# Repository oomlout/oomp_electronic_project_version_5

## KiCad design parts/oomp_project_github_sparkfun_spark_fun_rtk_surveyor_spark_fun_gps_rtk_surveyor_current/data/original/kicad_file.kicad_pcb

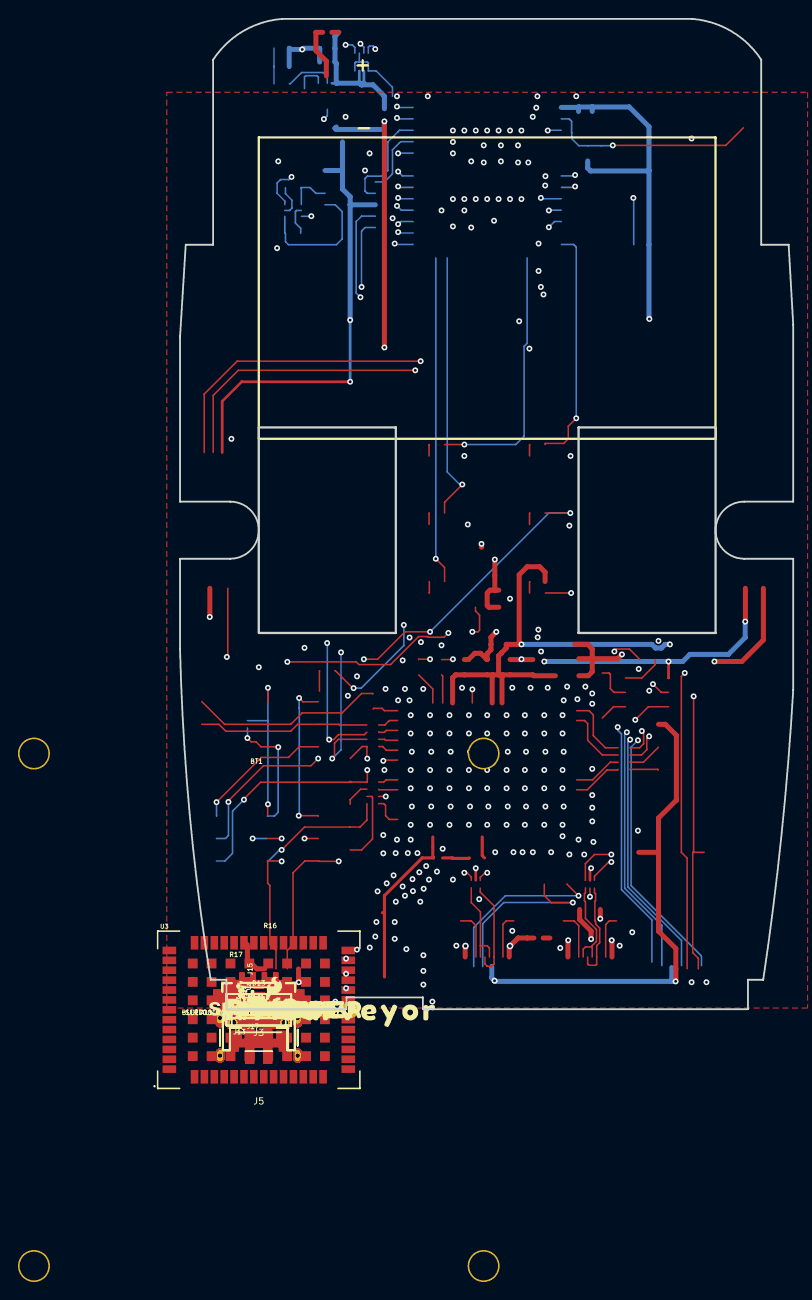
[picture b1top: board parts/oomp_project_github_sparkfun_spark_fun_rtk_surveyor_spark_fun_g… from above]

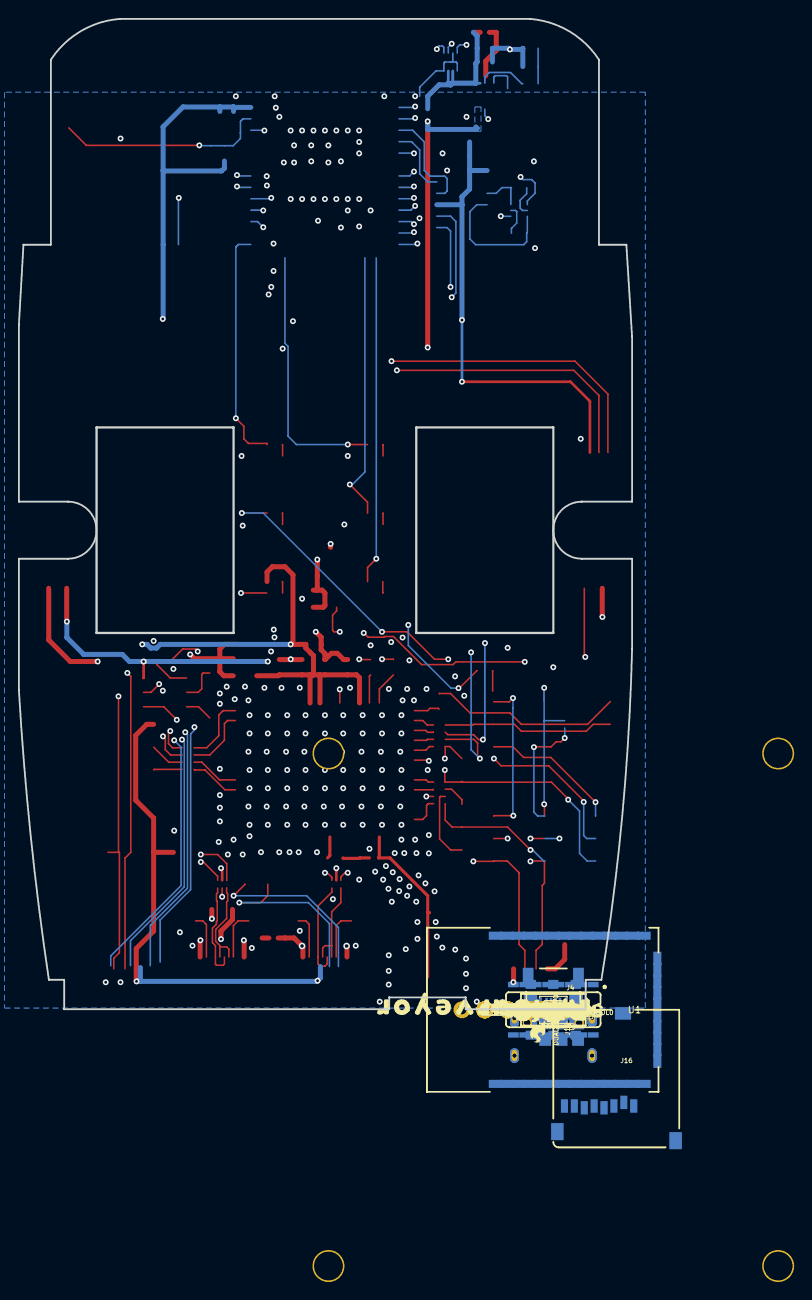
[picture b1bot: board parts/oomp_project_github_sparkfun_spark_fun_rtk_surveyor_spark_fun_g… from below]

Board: 4 copper layers, 68.2 x 110.1 mm, 199 parts (55 on the bottom side), 95 nets.

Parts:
BLUETOOTH_BROADCAST0: SWITCH_DPDT_SMD_AYZ0202
BT1: LIPO-OUTLINE1000; LIPO-1000
C1: 47pF; 0402
C2, C4, C6, C17, C18: 1.0uF; 0603
C5, C7, C11, C12, C13, C15, C16: 0.1uF; 0603
C8, C9: 4.7uF; 0603
C10, C14: 10uF; 0603
D1: Yellow; LED-0603
D2, D6: PRTR5V0U2F; SOT886
D3: WHITE; LED-0603
D4: BLUE; LED-0603
D7, D9: 3A/10V/280mV; SOD-323
D8, D10, D11: GREEN; LED-0603
D12: RED; LED-0603
D13: LED-TRICOLOR-5050
D14: PESD0402; 0402
DUAL_OUTPUT0: SMT-JUMPER_2_NO_SILK
E1: SMA; SMA-EDGE
FB1: 2.66Ω; 0402-TIGHT
FRAME1: FRAME-LETTERNO_PACKAGE; DUMMY
FRAME2: FRAME-LEDGER; CREATIVE_COMMONS
J1, J11, J12: 1X04_NO_SILK
J2, J9: JST-4-SMD-1.25MM-LOCKING
J3, J5: USB Female Type C Connector; USB-C-16P_4LAYER-PADS
J4: Qwiic Right Angle; JST04_1MM_RA
J6: Start Base; JST-2-SMD
J7: Power Switch; JST-2-SMD
J8: JST-2-SMD
J10, J14, J15: 1X02_NO_SILK
J13: Internal; JST04_1MM_RA
J16: microSD; MICRO-SD-SOCKET
J17: Qwiic Right Angle; 1X04_NO_SILK
J18: 1X05_NO_SILK
JP21, JP61, JP71, JP81: FIDUCIALUFIDUCIAL; FIDUCIAL-MICRO
LOGO1: OSHW-LOGOMINI; OSHW-LOGO-MINI
LOGO2, LOGO3: SFE_LOGO_NAME_FLAME.1_INCH; SFE_LOGO_NAME_FLAME_.1
MEAS0, MEAS1: COMBO-JUMPER_2_NC_TRACE
Q2: MBT3904DW1T1; SC70-6
R1: 4.7k; 0603
R2, R4, R9: 33; 1206_RA
R3: 33; 0603
R5: 0; 0603
R6, R7, R8: 1k; 0603
R10, R12, R34: 330; 0603
R11, R24, R25, R26: 20; 0603
R13, R15: 100k; 0603
R14: 10; 0603
R16, R17, R37, R38: 5.1k; 0603
R18, R20, R23, R29: 10k; 0603
R27, R28: 27; 0603
R30: 150k; 0603
SERIAL1_CONNECTION0: SWITCH_DPDT_SMD_AYZ0202
U1: ESP-WROOM-3232D-NARROW; ESP-WROOM-32D-NARROW
U2, U4: 3.3V; SOT23-5
U3: U-BLOX_ZED-F9P; ZED-F9P
U6: CH340C; SO016
U7: MAX17048; DFN-8
U10: MCP73833; DFN-10
U$1, U$38, U$48, U$82: #GND#0
U$2: SPECIAL_INSTRUCTIONS-ORDERING; ORDERING_INSTRUCTIONS
U$3, U$34: ROCKER_SWITCH
U$4: #BASE#0
U$5, U$37, U$47: #3V3#0
U$6: ANTENNA0
U$7, U$74: RTK0
U$8: #CHG#0
U$9, U$71: _SURVEYOR3
U$10: #RTK#1
U$11: #PPS#0
U$12: #RTK#0
U$13, U$15, U$21, U$69, U$75, U$76, U$77, U$78: LIGHT_PIPE_3MM
U$14: #RX#2
U$16: ZED0
U$17: ##SAFE##5
U$18: ACTIVE0
U$19: L1#L21
U$20: #PAIR#0
U$22: BASE2
U$23: #3#5#5V#0
U$24: #PPS#1
U$25: #PWR#2
U$26: 1553DBK-ENCLOSURE
U$27: LIPO0
U$28: ##RST##4
U$29, U$63: SERIAL10
U$30, U$93: QWIIC_4MM
U$31: OFF1
U$32: #FENCE#3
U$33: #INT#0
U$35: U#BLOX0
U$36, U$66: USB1
U$39: #RX2#2
U$40: #TX2#1
U$41: BLUETOOTH2
U$42: ON0
U$43: SERIAL20
U$44: ROVER3
U$45, U$68: #RX1#2
U$46, U$65: #TX1#1
U$49, U$52: NMEA1
U$50: RADIO0
U$51: BROADCAST3
U$53: RTCM0
U$54: BASE0
U$55, U$57: SWITCH1
U$56: POWER0
U$58: BLUEOOTH3
U$59: CNTR1
U$60: #ESP_RST#0
U$61: EXT0
U$62: NMEA2
U$64: CONNECTION1
U$67: ESP320
U$70: #GND#2
U$72: #TX#1
U$73: #DUAL#0
U$79: #1CM#0
U$80: #10CM#1
U$81: #100CM#2
U$83: MICROSD0
U$84: #GND#1
U$85: #3V3#2
U$86: #SCL#1
U$87: #SDA#0
U$88: #D_SEL#0
U$89: DATA2
U$90: PORT3
U$91: PPS#RESET0
U$92: NMEA#SERIAL1
U$94, U$95: V170
ZED_CONTROL0: SWITCH_DPDT_SMD_AYZ0202

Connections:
3.3V: C2.1, C4.1, C5.2, C7.2, C10.1, C11.1, C13.1, C14.1, C16.1, J1.4, J2.1, J4.2, J12.4, J13.2, J16.VCC, J17.2, R12.2, R13.2, R15.2, R20.2, U1.2, U2.5, U3.33, U3.34, U3.38, U6.4, U6.16
5V: C6.1, J7.1, J9.1, J11.4, U2.1, U2.3
ANT_VCC: C1.1, FB1.2, R14.1
BACKUP: C18.1, U3.36, U4.5
CC1: J5.A5, R17.2
CC2: J5.B5, R16.2
CC3: J3.B5, R37.2
CC4: J3.A5, R38.2
CHG_LED: R1.2, U10.3
CHG_THERM1: R5.2, R18.2, R30.2
D+: D6.4, R27.1
D+1: D2.4, U6.5
D-: D6.6, R28.1
D-1: D2.6, U6.6
ESP32_EN: C12.1, J14.1, Q2.3, R20.1, U1.3
ESP32_RXI: U1.34, U6.2
ESP32_TXO: U1.35, U6.3
ESP32_~DTR: Q2.1, R23.1, U6.13
ESP32_~RTS: Q2.4, R29.1, U6.14
ESP_0/BOOT: Q2.6, U1.25
ESP_2/LED_1CM: R26.1, U1.24
ESP_4/LED_BASE_STAT: R34.1, U1.26
ESP_5/SWITCH_BASE_SELECT: J6.1, U1.29
ESP_12/LED_BLUETOOTH: R10.1, U1.14
ESP_13/LED_100CM: R24.1, U1.16
ESP_15/LED_10CM: R25.1, U1.23
ESP_16/BT_RXI: BLUETOOTH_BROADCAST0.2, U1.27
ESP_17/BT_TXO: BLUETOOTH_BROADCAST0.5, U1.28
ESP_18/SD_SCK: J16.SCLK, U1.30
ESP_19/SD_CIPO: J16.DO/DAT0, U1.31
ESP_21/SDA: J4.3, J13.3, J17.3, R9.P6, U1.33, U7.8
ESP_22/SCL: J4.4, J13.4, J17.4, R9.P7, U1.36, U7.7
ESP_23/SD_COPI: J16.DI/CMD, U1.37
ESP_25/SD_~CS: J16.CS/DAT3, R13.1, U1.10
ESP_26/ZED_TX_READY: J18.1, R9.P8, U1.11
ESP_26/ZED_TX_READY_LV: R9.P1, U3.46
ESP_27/ZED_~RESET: J18.2, R2.P5, U1.12, ZED_CONTROL0.4
ESP_27/ZED_~RESET_LV: R2.P4, U3.49
ESP_32/PWR_LVL_RED: D13.5, U1.8
ESP_33/PWR_LVL_GRN: D13.4, U1.9
ESP_36/BATT_ALRT: U1.4, U7.5
ESP_D1+: D2.3, J3.A6, J3.B6
ESP_D1-: D2.1, J3.A7, J3.B7
EXTERNAL_SERIAL1_RXI: SERIAL1_CONNECTION0.4, ZED_CONTROL0.6
EXTERNAL_SERIAL1_RXI/ZED_~RESET: J2.3, J12.2, ZED_CONTROL0.5
EXTERNAL_SERIAL1_TXO: DUAL_OUTPUT0.2, SERIAL1_CONNECTION0.1, ZED_CONTROL0.3
EXTERNAL_SERIAL1_TXO/PPS: J2.2, J12.3, ZED_CONTROL0.2
FENCE_LV: R4.P8, U3.19
GND: C1.2, C2.2, C4.2, C5.1, C6.2, C7.1, C8.2, C9.2, C10.2, C11.2, C12.2, C13.2, C14.2, C15.2, C16.2, C17.2, C18.2, D1.C, D2.2, D4.C, D6.2, D8.C, D10.C, D11.C, D12.C, D14.2, E1.GND@0, E1.GND@1, E1.GND@2, E1.GND@3, J1.1, J2.4, J3.GND, J3.GND2, J3.SHLD1, J3.SHLD2, J3.SHLD3, J3.SHLD4, J4.1, J5.GND, J5.GND2, J5.SHLD1, J5.SHLD2, J5.SHLD3, J5.SHLD4, J6.2, J8.1, J9.4, J10.2, J11.1, J12.1, J13.1, J14.2, J16.CD1, J16.GND, J16.GND1, J16.GND3, J17.1, R6.2, R7.1, R8.2, R15.1, R16.1, R17.1, R18.1, R30.1, R37.1, R38.1, U1.1, U1.15, U1.38, U1.GND1, U1.GNDT1, U1.GNDT2, U1.GNDT3, U1.GNDT4, U1.GNDT5, U1.GNDT6, U1.GNDT7, U1.GNDT8, U2.2, U3.1, U3.3, U3.12, U3.14, U3.32, U3.37, U3.41, U3.48, U3.55, U3.56, U3.57, U3.58, U3.59, U3.60, U3.61, U3.62, U3.63, U3.64, U3.65, U3.66, U3.67, U3.68, U3.69, U3.70, U3.71, U3.72, U3.73, U3.74, U3.75, U3.76, U3.77, U3.78, U3.79, U3.80, U3.81, U3.82, U3.83, U3.84, U3.85, U3.86, U3.87, U3.88, U3.89, U3.90, U3.91, U3.92, U3.93, U3.94, U3.95, U3.96, U3.97, U3.98, U3.99, U3.100, U3.101, U3.102, U4.2, U6.1, U7.1, U7.4, U7.6, U7.9, U10.5, U10.11
GPS_ANT1: D14.1, E1.SIG, FB1.1, U3.2
LIPO_RAW: J8.2, MEAS1.1, MEAS1.3
unnamed: D3.A, R12.1
unnamed: D1.A, R11.1
unnamed: D4.A, R10.2
unnamed: J5.VBUS1, J5.VBUS2, MEAS0.1, MEAS0.3
unnamed: R5.1, U10.8
unnamed: D13.1, R1.1
unnamed: D13.3, R6.1
unnamed: D13.2, R8.1
unnamed: R27.2, U3.40
unnamed: R28.2, U3.39
unnamed: R14.2, U3.7
unnamed: Q2.5, R23.2
unnamed: Q2.2, R29.2
unnamed: D8.A, R24.2
unnamed: D10.A, R25.2
unnamed: D11.A, R26.2
unnamed: D12.A, R34.2
unnamed: D9.A, J3.VBUS1, J3.VBUS2
NMEA-RX: BLUETOOTH_BROADCAST0.6, SERIAL1_CONNECTION0.6
NMEA-TX: BLUETOOTH_BROADCAST0.3, DUAL_OUTPUT0.1, SERIAL1_CONNECTION0.3
PPS: R2.P1, U3.53
PROG1: R7.2, U10.6
RTK_LV: R4.P7, U3.20
RX2_LV: R4.P6, U3.26
RXLV: R9.P4, U3.43
SCL_LV: R9.P2, U3.45
SDA_LV: R9.P3, U3.44
TX2_LV: R4.P5, U3.27
TXLV: R3.1, U3.42
UNP_D+: D6.3, J5.A6, J5.B6
UNP_D-: D6.1, J5.A7, J5.B7
VIN: C9.1, D2.5, D6.5, D7.C, D9.C, D13.6, J7.2, MEAS0.2, MEAS0.4, U10.1, U10.2
V_BATT: C8.1, C15.1, C17.1, D7.A, J10.1, MEAS1.2, MEAS1.4, U4.1, U4.3, U7.2, U7.3, U10.9, U10.10
ZED-RXI1: J15.2, R9.P5, SERIAL1_CONNECTION0.5
ZED-RXI2: BLUETOOTH_BROADCAST0.4, J9.3, J11.2, R4.P3
ZED-TXO1: J15.1, R3.2, SERIAL1_CONNECTION0.2
ZED-TXO2: BLUETOOTH_BROADCAST0.1, J9.2, J11.3, R4.P4
ZED_D_SEL: J18.5, R2.P7
ZED_D_SEL_LV: R2.P2, U3.47
ZED_FENCE_STAT: J1.2, R4.P1
ZED_PPS_STAT: J18.4, R2.P8, R11.2, ZED_CONTROL0.1
ZED_RTK_STAT: D3.C, J1.3, R4.P2
ZED_~SAFE: J18.3, R2.P6
ZED_~SAFE_LV: R2.P3, U3.50

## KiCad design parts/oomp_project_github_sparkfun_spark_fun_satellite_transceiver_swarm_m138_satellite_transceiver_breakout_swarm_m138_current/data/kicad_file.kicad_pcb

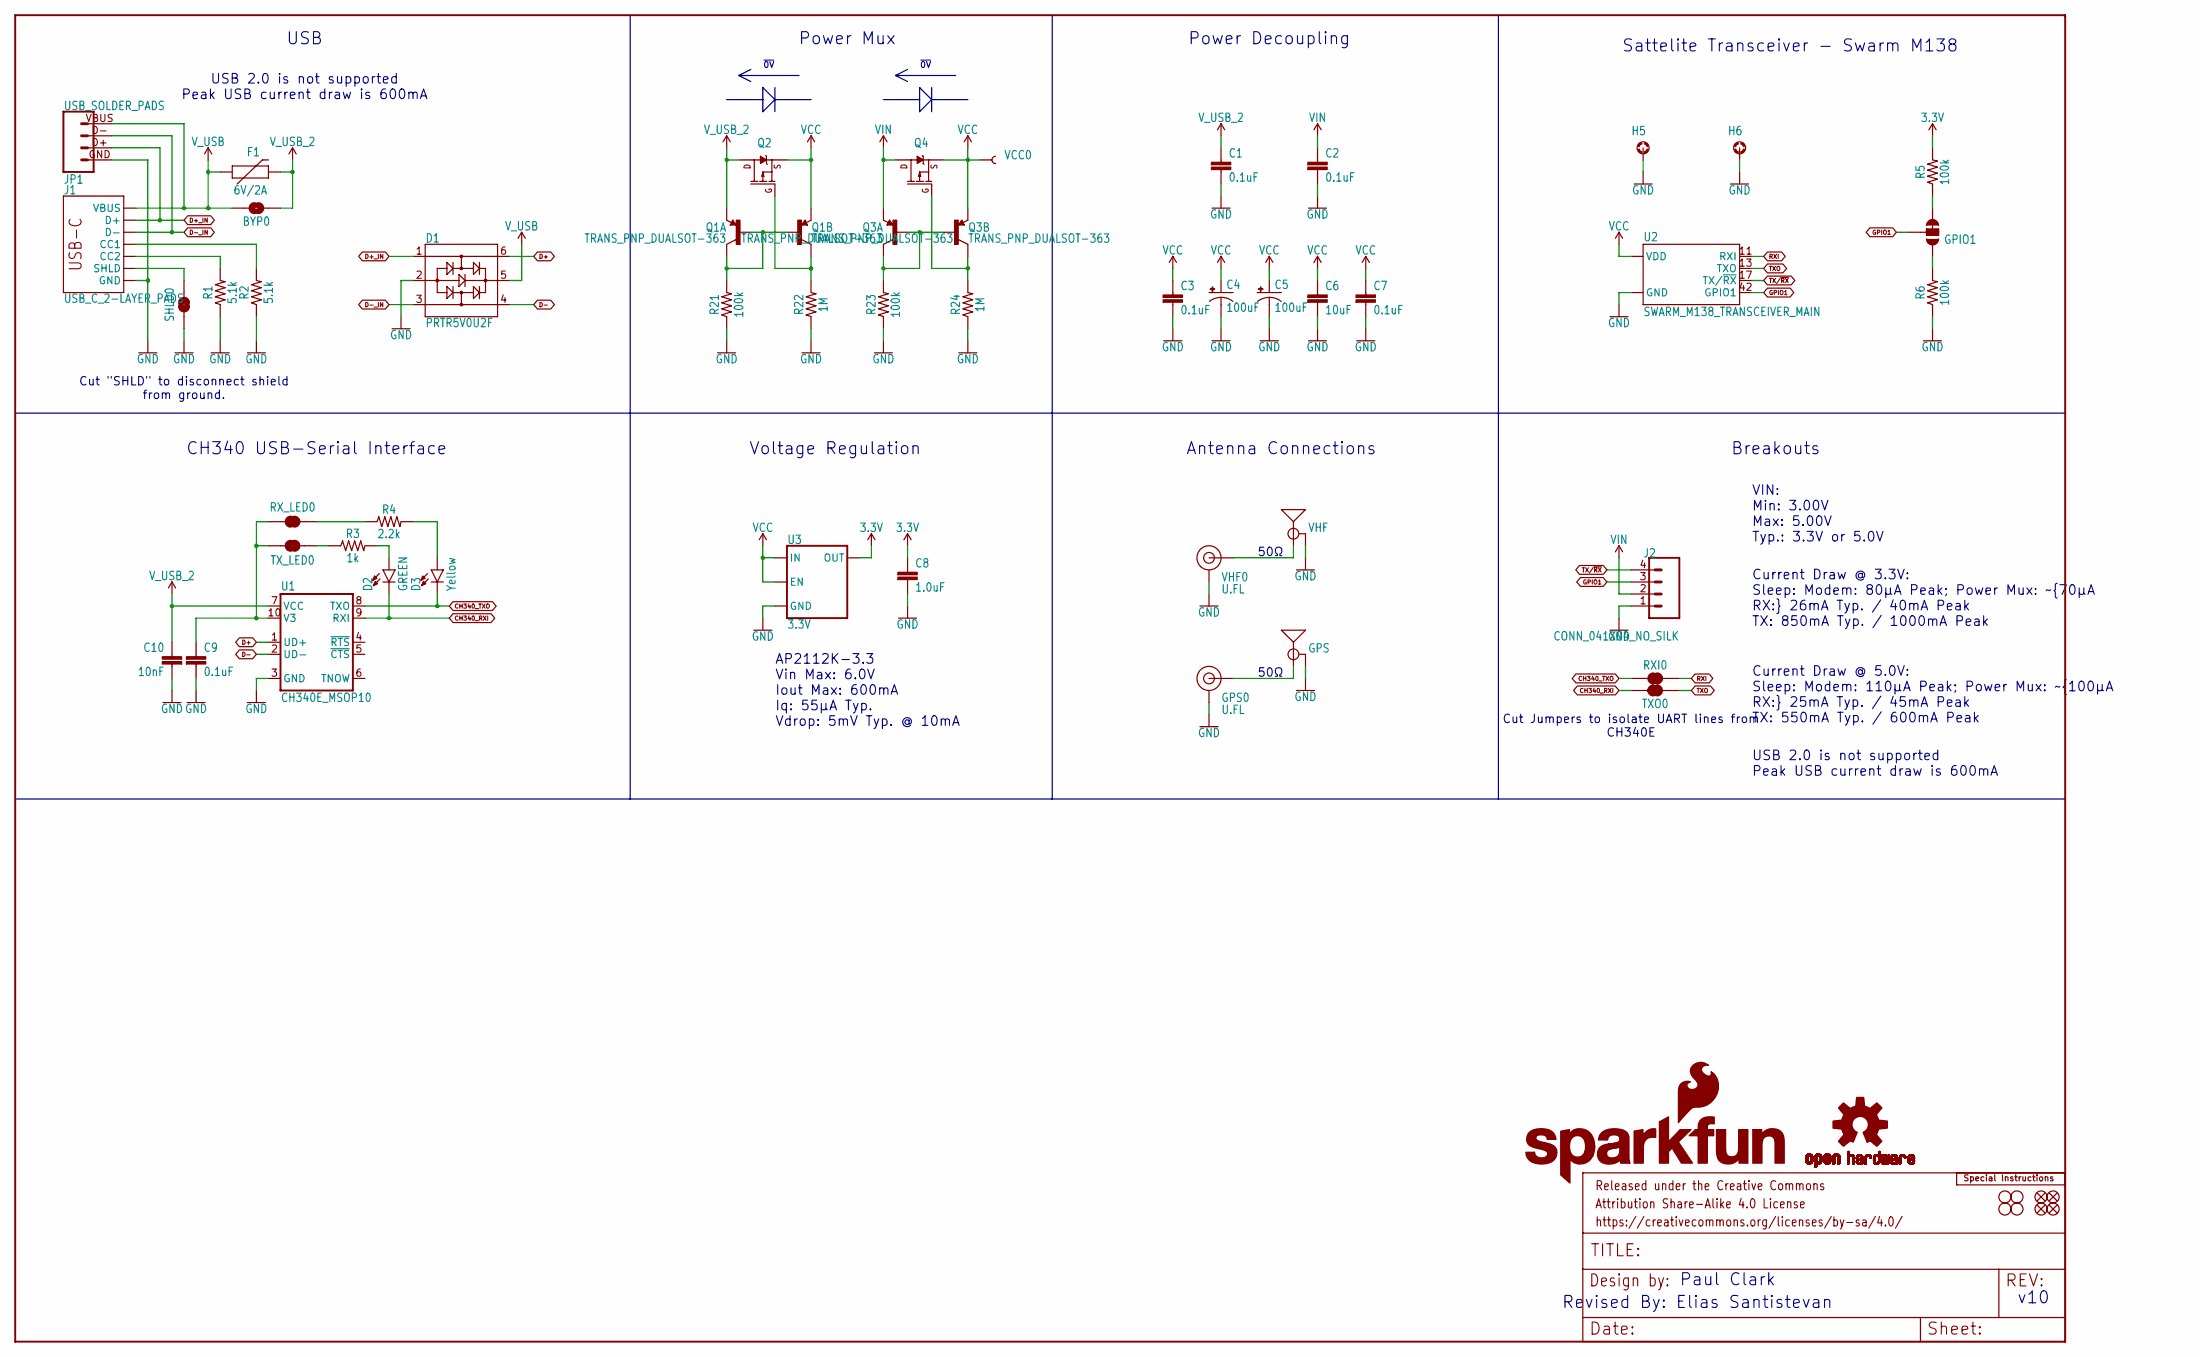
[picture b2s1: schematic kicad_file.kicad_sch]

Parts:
BYP0: JUMPER-SMT_2_NO_SILK; SMT-JUMPER_2_NO_SILK
C1, C2, C3, C7, C9: 0.1uF; 0603
C4, C5: 100uF; PANASONIC_D
C6: 10uF; 0603
C8: 1.0uF; 0603
C10: 10nF; 0603
D1: PRTR5V0U2F; SOT886
D2: GREEN; LED-0603
D3: Yellow; LED-0603
E1: VHF; SMA-EDGE
E2: GPS; SMA-EDGE
F1: 6V/2A; 1210
FD1, FD2, FD3, FD4: FIDUCIAL1X2; FIDUCIAL-1X2
FRAME1: FRAME-LEDGER; CREATIVE_COMMONS
GPIO1: JUMPER-SMT_3_1-NC_TRACE_SILK; SMT-JUMPER_3_1-NC_TRACE_SILK
GPS0: U.FL
H1, H2, H3, H4: STAND-OFF
H5, H6: STAND-OFF-REFLOW-M2.5_1.5MM_TALL; STAND-OFF-REFLOW-M2.5
J1: USB_C_2-LAYER_PADS; USB-C-16P-2LAYER-PADS
J2: CONN_041X04_NO_SILK; 1X04_NO_SILK
JP1: USB_SOLDER_PADS; USB-SOLDER-PADS
LOGO1: SPECIAL_INSTRUCTIONS-ORDERING; ORDERING_INSTRUCTIONS
LOGO2: OSHW-LOGOM; OSHW-LOGO-M
LOGO4: SFE_LOGO_NAME_FLAME.1_INCH; SFE_LOGO_NAME_FLAME_.1
Q1, Q3: TRANS_PNP_DUALSOT-363; SOT363_PHILIPS
Q2, Q4: 20V/4.2A/52mΩ/1.4W; SOT23-3
R1, R2: 5.1k; 0603
R3: 1k; 0603
R4: 2.2k; 0603
R5, R6, R21, R23: 100k; 0603
R22, R24: 1M; 0603
RXI0: JUMPER-COMBO_2_NC_TRACE; COMBO-JUMPER_2_NC_TRACE
RX_LED0: JUMPER-SMT_2_NC_TRACE_SILK; SMT-JUMPER_2_NC_TRACE_SILK
SHLD0: JUMPER-SMT_2_NC_TRACE_SILK; SMT-JUMPER_2_NC_TRACE_SILK
TXO0: JUMPER-COMBO_2_NC_TRACE; COMBO-JUMPER_2_NC_TRACE
TX_LED0: JUMPER-SMT_2_NC_TRACE_SILK; SMT-JUMPER_2_NC_TRACE_SILK
U1: CH340E_MSOP10; MSOP10
U2: SWARM_M138_TRANSCEIVER_MAIN; M.2-SWARM-M138-A
U3: 3.3V; SOT23-5
VCC0: TEST-POINT3X5; PAD.03X.05
VHF0: U.FL

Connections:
3.3V: C8.1, R5.2, U3.5 (OUT)
CH340_RXI: D2.C, TXO0.2, TXO0.4 (2), U1.9 (RXI)
CH340_TXO: D3.C, RXI0.1, RXI0.3 (1), U1.8 (TXO)
D+: D1.6, U1.1 (UD+)
D+_IN: D1.1, J1.A6 (D+), J1.B6 (D+), JP1.D+ (3)
D-: D1.4, U1.2 (UD-)
D-_IN: D1.3, J1.A7 (D-), J1.B7 (D-), JP1.D- (2)
GND: C1.2, C2.2, C3.2, C4.-, C5.-, C6.2, C7.2, C8.2, C9.2, C10.2, D1.2, E1.GND@0 (GND), E1.GND@1 (GND), E1.GND@2 (GND), E1.GND@3 (GND), E2.GND@0 (GND), E2.GND@1 (GND), E2.GND@2 (GND), E2.GND@3 (GND), GPS0.1 (GND), GPS0.2 (GND), H5.1, H6.1, J1.GND, J1.GND2 (GND), J2.1, JP1.GND (4), R1.1, R2.1, R6.1, R21.1, R22.1, R23.1, R24.1, SHLD0.1, U1.3 (GND), U2.4 (GND), U2.9 (GND), U2.15 (GND), U2.18 (GND), U2.21 (GND), U2.26 (GND), U2.27 (GND), U2.29 (GND), U2.34 (GND), U2.35 (GND), U2.37 (GND), U2.40 (GND), U2.43 (GND), U2.50 (GND), U2.A1 (GND), U2.A2 (GND), U3.2 (GND), VHF0.1 (GND), VHF0.2 (GND)
GPIO1: GPIO1.2, J2.3, U2.42 (GPIO1)
GPS: E2.SIG (SIGNAL), GPS0.FEED (SIGNAL)
unnamed: J1.B5 (CC2), R1.2
unnamed: J1.A5 (CC1), R2.2
unnamed: Q1.2 (B), Q1.5 (B), Q1.6 (C), R21.2
unnamed: C9.1, RX_LED0.1, TX_LED0.2, U1.10 (V3)
unnamed: R4.1, RX_LED0.2
unnamed: D2.A, R3.2
unnamed: D3.A, R4.2
unnamed: R3.1, TX_LED0.1
unnamed: Q1.3 (C), Q2.1 (G), R22.2
unnamed: GPIO1.3, R5.1
unnamed: Q3.2 (B), Q3.5 (B), Q3.6 (C), R23.2
unnamed: GPIO1.1, R6.2
unnamed: Q3.3 (C), Q4.1 (G), R24.2
RXI: RXI0.2, RXI0.4 (2), U2.11 (RXI)
SHLD: J1.SHLD1 (SHLD), J1.SHLD2 (SHLD), J1.SHLD3 (SHLD), J1.SHLD4 (SHLD), SHLD0.2
TX/~RX: J2.4, U2.17 (TX/~RX)
TXO: TXO0.1, TXO0.3 (1), U2.13 (TXO)
VCC: C3.1, C4.+, C5.+, C6.1, C7.1, Q1.4 (E), Q2.2 (S), Q3.4 (E), Q4.2 (S), U2.2 (VDD), U2.39 (VDD), U2.41 (VDD), U2.52 (VDD), U3.1 (IN), U3.3 (EN), VCC0.1
VHF: E1.SIG (SIGNAL), VHF0.FEED (SIGNAL)
VIN: C2.1, J2.2, Q3.1 (E), Q4.3 (D)
V_USB: BYP0.2, D1.5, F1.1, J1.VBUS1 (VBUS), J1.VBUS2 (VBUS), JP1.VBUS (1)
V_USB_2: BYP0.1, C1.1, C10.1, F1.2, Q1.1 (E), Q2.3 (D), U1.7 (VCC)

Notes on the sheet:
USB
Breakouts
Antenna Connections
AP2112K-3.3 Vin Max: 6.0V Iout Max: 600mA Iq: 55µA Typ. Vdrop: 5mV Typ. @ 10mA
Power Decoupling
Current Draw @ 5.0V: Sleep: Modem: 110µA Peak; Power Mux: ~{100µA RX:} 25mA Typ. / 45mA Peak TX: 550mA Typ. / 600mA Peak
Cut "SHLD" to disconnect shield from ground.
CH340 USB-Serial Interface
Power Mux
v10
50Ω
Paul Clark
Voltage Regulation
USB 2.0 is not supported Peak USB current draw is 600mA
VIN: Min: 3.00V Max: 5.00V Typ.: 3.3V or 5.0V
Revised By: Elias Santistevan
Sattelite Transceiver - Swarm M138
Cut Jumpers to isolate UART lines from CH340E
~{0V}
Current Draw @ 3.3V: Sleep: Modem: 80µA Peak; Power Mux: ~{70µA RX:} 26mA Typ. / 40mA Peak TX: 850mA Typ. / 1000mA Peak

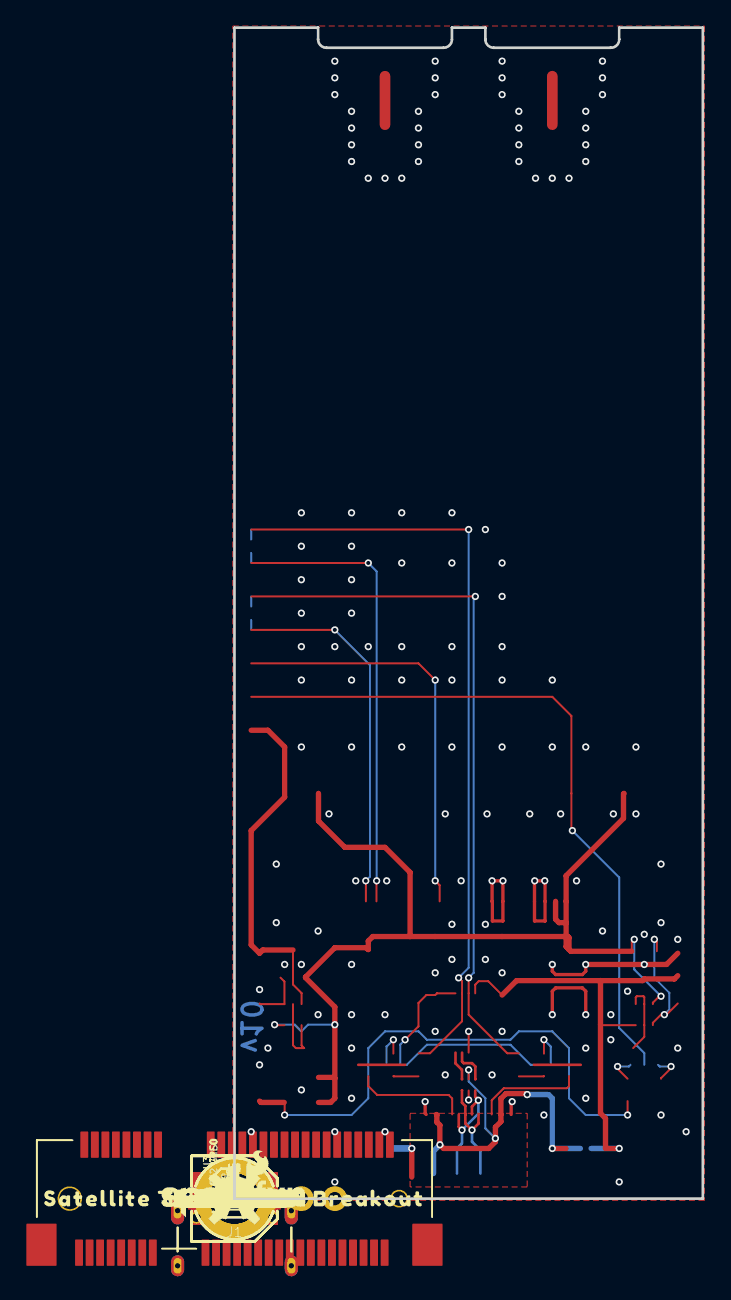
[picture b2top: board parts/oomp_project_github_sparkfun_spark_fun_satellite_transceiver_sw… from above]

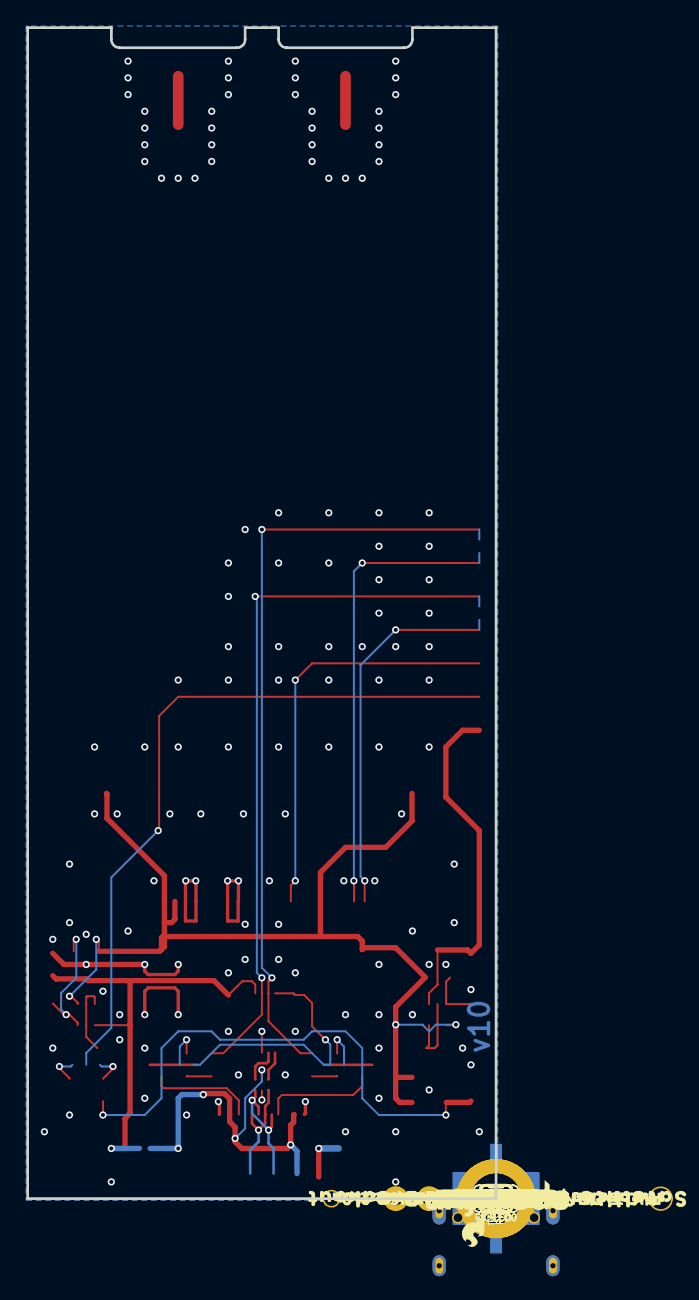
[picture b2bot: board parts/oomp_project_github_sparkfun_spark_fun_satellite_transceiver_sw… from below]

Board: 2 copper layers, 35.6 x 88.9 mm, 98 parts (35 on the bottom side), 32 nets.

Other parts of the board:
LOGO3: SFE_LOGO_NAME_FLAME.1_INCH; SFE_LOGO_NAME_FLAME_.1
U$1: #SHLD#14
U$3: VHF0
U$4: GPS0
U$5: VIN#__3#0V_MIN__5#0V_MAX0
U$6: PLEASE_CONSULT_THE_DOCUMENTATION0
U$7: #CH340_RXI#0
U$8: #CH340_RXI#341
U$9: #TXO#341
U$10: #TXO#342
U$11: #CH340_TXO#0
U$12: #CH340_TXO#341
U$13: #RXI#0
U$14: #RXI#1
U$15: #TX##RX##1
U$16: #TX##RX##0
U$17: #GPIO1_#2
U$18: V0
U$19: #GPIO1#0
U$20: #_GPIO1#2
U$21, U$22: #VIN#0
U$23, U$24: #GND#0
U$25: TX0
U$26: RX0
U$27: #TX_LED#0
U$28: #RX_LED#0
U$29: #BYPASS#0
U$30: G3
U$31: FOR_THE_PEAK_TRANSMIT_CURRENT1
U$32: NOT_COMPATIBLE_WITH_USB_2#02
U$34, U$39: SATELLITE_TRANSCEIVER_BREAKOUT0
U$36: D#2
U$37: D#1
U$40, U$41: SWARM_M1381

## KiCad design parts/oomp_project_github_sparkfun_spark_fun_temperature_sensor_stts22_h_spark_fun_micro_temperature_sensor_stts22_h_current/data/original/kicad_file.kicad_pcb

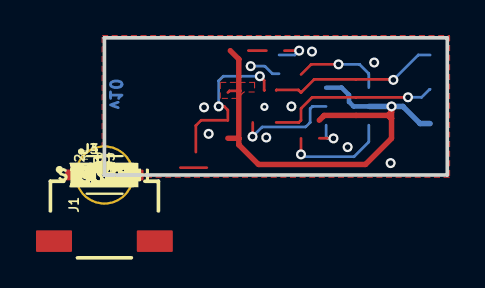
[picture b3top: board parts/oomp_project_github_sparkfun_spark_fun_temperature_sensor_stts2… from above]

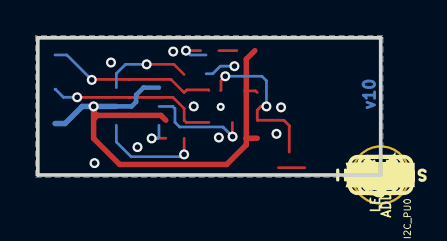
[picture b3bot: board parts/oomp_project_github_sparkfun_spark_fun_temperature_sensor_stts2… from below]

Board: 2 copper layers, 19.1 x 7.6 mm, 40 parts (20 on the bottom side), 11 nets.

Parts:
ADDR0: JUMPER-SMT_3_1-NC_TRACE_SILK; SMT-JUMPER_3_1-NC_TRACE_SILK
C1: 0.1uF; 0402-TIGHT
D1: RED; LED-0402
FD1, FD2: FIDUCIALUFIDUCIAL; FIDUCIAL-MICRO
FID1, FID2: FIDUCIALUFIDUCIAL; FIDUCIAL-MICRO
FRAME1: FRAME-LETTER; CREATIVE_COMMONS
I2C_PU0: S_MODE; SMT-JUMPER_3_2-NC_TRACE_SILK
J1: Qwiic Right Angle; JST04_1MM_RA
J3, J4: 1X01_1MM_NO_SILK
LED0: JUMPER-SMT_2_NC_TRACE_SILK; SMT-JUMPER_2_NC_TRACE_SILK
LOGO1: QWIIC_LOGO_3MM; QWIIC_3MM
LOGO2: OSHW-LOGOMINI; OSHW-LOGO-MINI
LOGO3: SFE_LOGO_NAME_FLAMEBLANK; BLANK
R1, R2, R4: 2.2k; 0402-TIGHT
R3: 10k; 0402-TIGHT
R5: 15K; 0402-TIGHT
STANDOFF1: STAND-OFFTIGHT; STAND-OFF-TIGHT
TP1, TP2, TP3, TP4: TEST-POINT3; PAD.03X.03
U2: STTS22H; UDFN-6L
U$1: #0#4
U$2: #1#4
U$3: #LED#2121
U$4, U$10: #GND#4
U$5, U$6: ##INT##9
U$7, U$8: STTS22H11
U$9: TEMP24
U$11: SENSOR25
U$12: #I2C#4
U$29: SFE_LOGO_FLAME_.1

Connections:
3.3V: ADDR0.1, C1.1, I2C_PU0.2, J1.2, R3.2, R4.2, R5.2, TP3.1, U2.P3
ADDR: ADDR0.2, U2.P4
GND: C1.2, J1.1, J4.1, LED0.1, TP4.1, U2.P5, U2.P7
unnamed: ADDR0.3, R5.1
unnamed: D1.A, R4.1
unnamed: D1.C, LED0.2
unnamed: I2C_PU0.1, R1.2
unnamed: I2C_PU0.3, R2.2
SCL: J1.4, R1.1, TP1.1, U2.P1
SDA: J1.3, R2.1, TP2.1, U2.P6
~INT: J3.1, R3.1, U2.P2

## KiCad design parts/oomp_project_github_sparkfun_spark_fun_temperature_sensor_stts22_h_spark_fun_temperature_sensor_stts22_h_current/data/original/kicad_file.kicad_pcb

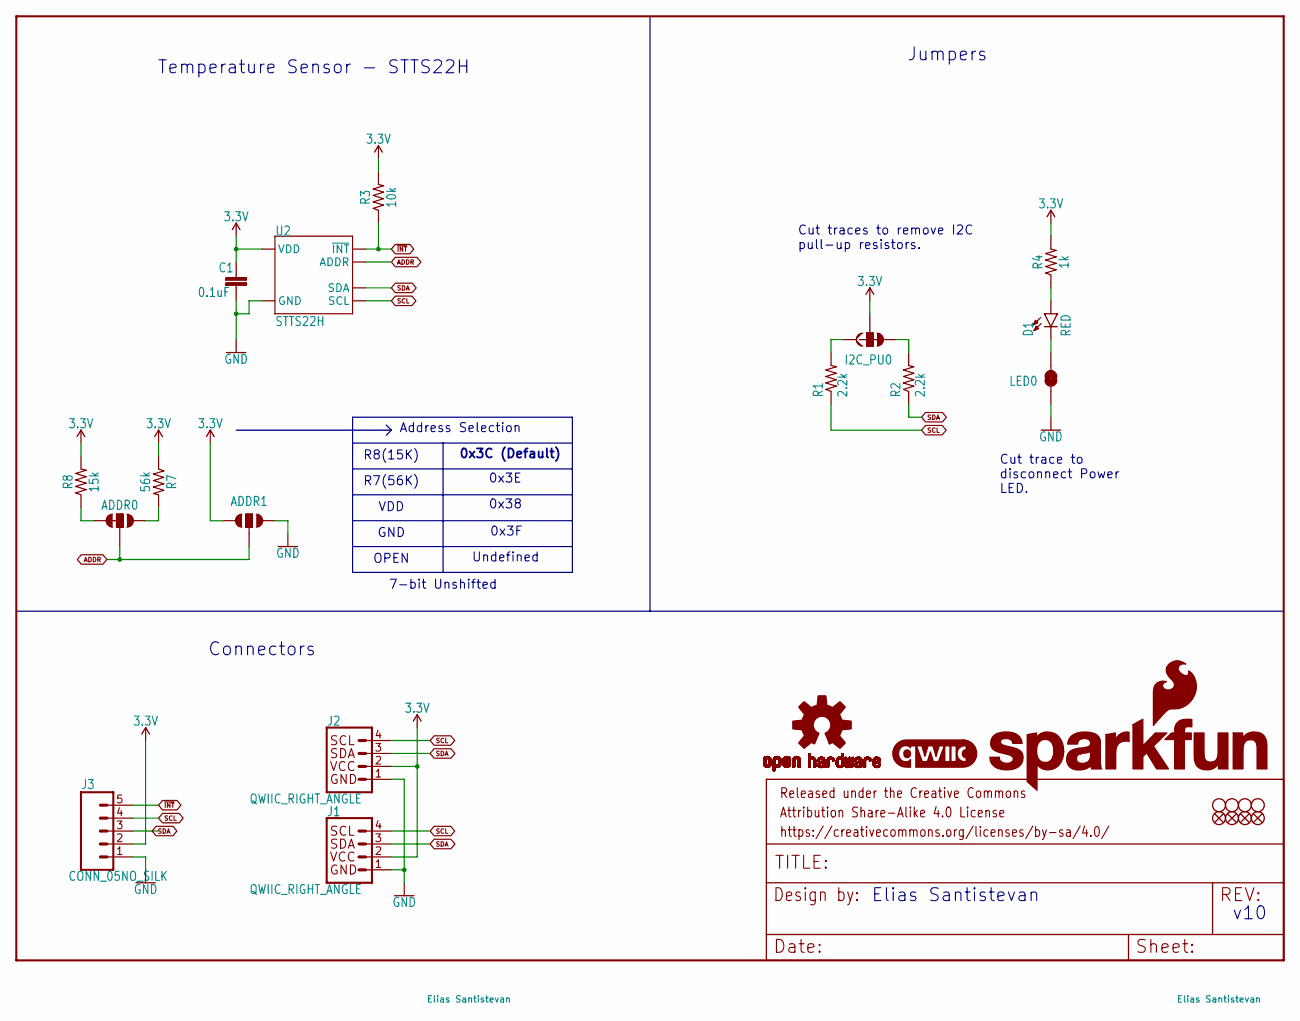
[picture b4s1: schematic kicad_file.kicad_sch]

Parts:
ADDR0: JUMPER-SMT_3_1-NC_TRACE_SILK; SMT-JUMPER_3_1-NC_TRACE_SILK
ADDR1: JUMPER-SMT_3_NO_SILK; SMT-JUMPER_3_NO_SILK
C1: 0.1uF; 0603
D1: RED; LED-0603
FD1, FD2, FD3, FD4: FIDUCIAL1X2; FIDUCIAL-1X2
FRAME1: FRAME-LETTER; CREATIVE_COMMONS
I2C_PU0: S_MODE; SMT-JUMPER_3_2-NC_TRACE_SILK
J1, J2: QWIIC_RIGHT_ANGLE; JST04_1MM_RA
J3: CONN_05NO_SILK; 1X05_NO_SILK
LED0: JUMPER-SMT_2_NC_TRACE_SILK; SMT-JUMPER_2_NC_TRACE_SILK
LOGO2: OSHW-LOGOMINI; OSHW-LOGO-MINI
LOGO3: SFE_LOGO_NAME_FLAME.1_INCH; SFE_LOGO_NAME_FLAME_.1
LOGO4: QWIIC_LOGO_4MM; QWIIC_4MM
R1, R2: 2.2k; 0603
R3: 10k; 0603
R4: 1k; 0603
R7: 56k; 0603
R8: 15k; 0603
STANDOFF1, STANDOFF2, STANDOFF3, STANDOFF5: STAND-OFFTIGHT; STAND-OFF-TIGHT
U2: STTS22H; UDFN-6L

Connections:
3.3V: ADDR1.3, C1.1, I2C_PU0.2, J1.2, J2.2, J3.2, R3.2, R4.2, R7.1, R8.2, U2.P3 (VDD)
ADDR: ADDR0.2, ADDR1.2, U2.P4 (ADDR)
GND: ADDR1.1, C1.2, J1.1, J2.1, J3.1, LED0.1, U2.P5 (GND), U2.P7 (GND)
unnamed: D1.A, R4.1
unnamed: D1.C, LED0.2
unnamed: ADDR0.3, R8.1
unnamed: I2C_PU0.1, R1.2
unnamed: I2C_PU0.3, R2.2
unnamed: ADDR0.1, R7.2
SCL: J1.4, J2.4, J3.4, R1.1, U2.P1 (SCL)
SDA: J1.3, J2.3, J3.3, R2.1, U2.P6 (SDA)
~INT: J3.5, R3.1, U2.P2 (~INT)

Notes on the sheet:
GND
Jumpers
Undefined
Cut traces to remove I2C pull-up resistors.
R8(15K)
v10
0x38
Cut trace to disconnect Power LED.
Elias Santistevan
0x3E
0x3C (Default)
OPEN
Connectors
R7(56K)
0x3F
Address Selection
VDD
7-bit Unshifted
Temperature Sensor - STTS22H

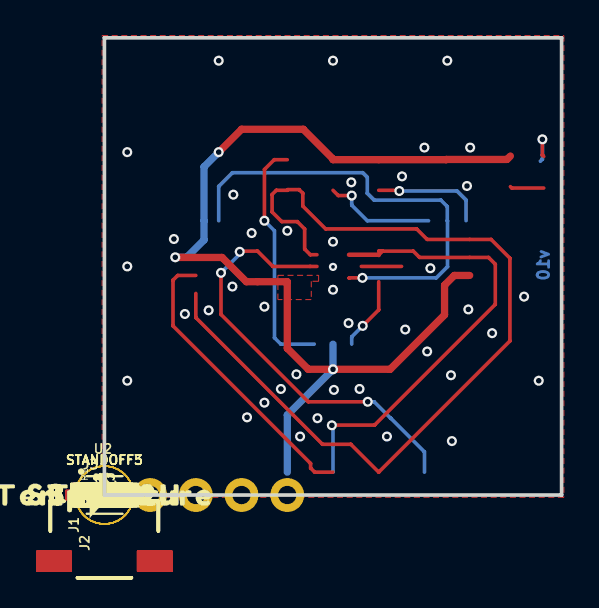
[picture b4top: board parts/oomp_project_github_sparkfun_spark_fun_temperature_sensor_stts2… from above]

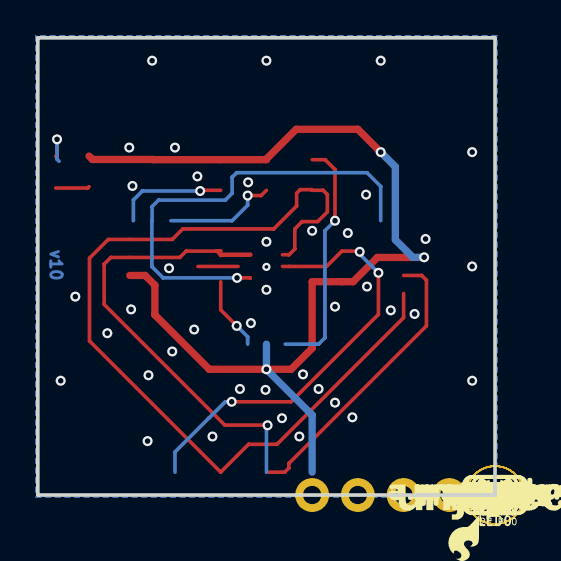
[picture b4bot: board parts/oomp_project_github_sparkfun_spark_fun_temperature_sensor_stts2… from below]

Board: 2 copper layers, 25.4 x 25.4 mm, 56 parts (26 on the bottom side), 12 nets.

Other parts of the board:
U$1, U$9: #GND#3
U$2, U$10: #3V3#4
U$3: #SDA#5
U$4: #SCL#4
U$5: #SDA#7
U$6: #ADDR#6
U$7: #SCL#6
U$8: #ADDR1#9
U$11: ##INT##9
U$12: #0X3C#25
U$13: #0X3E#25
U$14: #0X3F#25
U$15: #0X38#25
U$16: #LED#11
U$17, U$23: TEMPERATURE23
U$18: ##INT##6
U$19, U$24: SENSOR24
U$20: SFE_LOGO_FLAME_.1
U$21: PWR9
U$22, U$26: STTS22H21
U$25: #I2C#11
U$27: DEF_ADDR#29
U$28: 0X3C30

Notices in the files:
parts/oomp_project_github_sparkfun_spark_fun_rtk_reference_station_sticker_alignment_jig_sticker_current/data/kicad_file.kicad_sch:
Released under the Creative Commons
https://creativecommons.org/licenses/by-sa/4.0
parts and their libraries:
Released under the Creative Commons Attribution Share-Alike 4.0 License
